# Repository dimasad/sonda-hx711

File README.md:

sonda-hx711
===========

Circuito para uma sonda aerodinâmica de 5 furos utilizando sensores de pressão
diferencial piezoresistivos e circuitos integrados HX711 para aquisição
de dados.

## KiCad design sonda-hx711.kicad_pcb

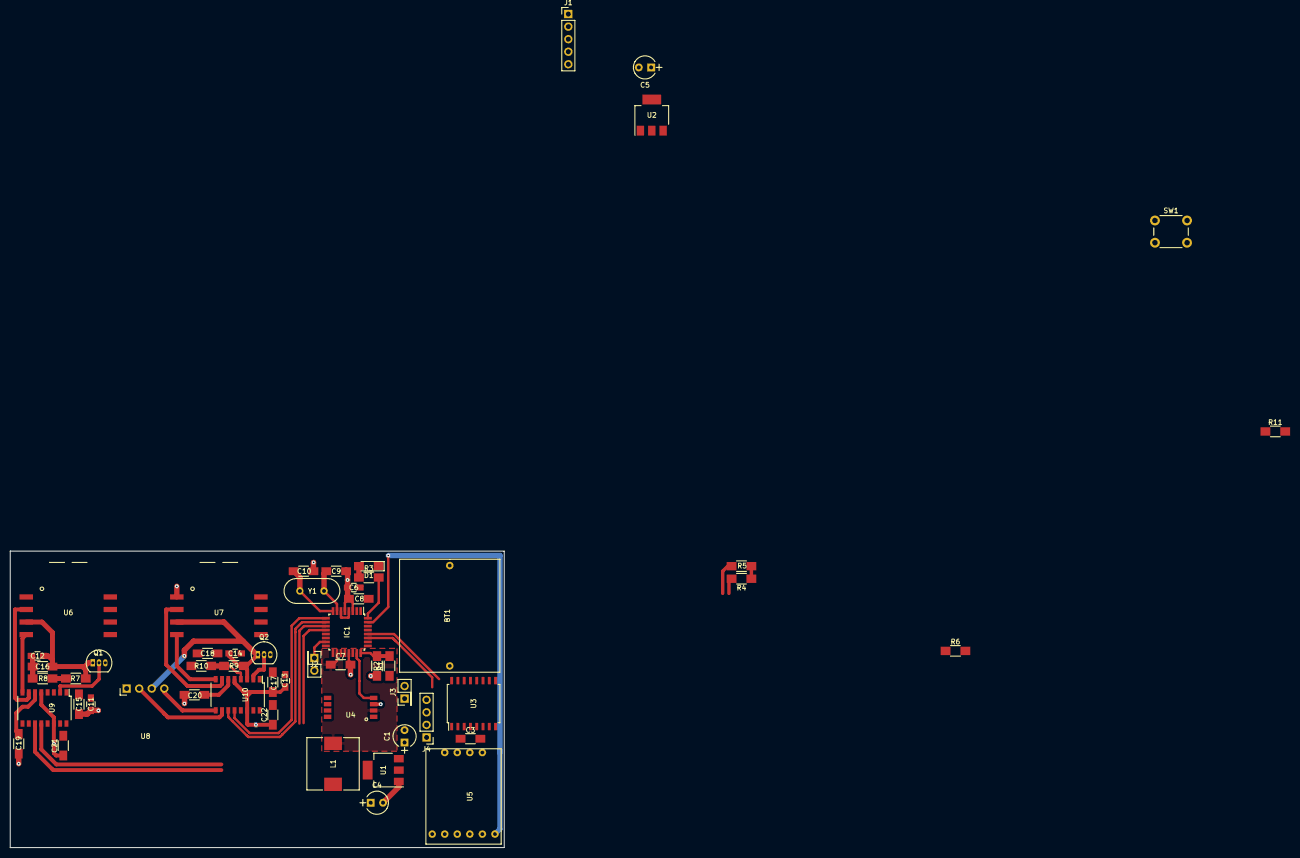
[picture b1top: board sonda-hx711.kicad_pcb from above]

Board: 2 copper layers, 100.0 x 60.0 mm, 54 parts (0 on the bottom side), 37 nets.

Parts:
BT1: 3V; SuporteBateria
C1, C4, C5: 22uF; CP_Radial_Tantal_D4.5mm_P2.50mm
C3, C7, C8, C15, C16, C17, C18, C19, C20, C21, C22: 100nF; C_1206_HandSoldering
C6, C11, C12, C13, C14: 10uF; C_0805_HandSoldering
C9, C10: 20pF; C_1206_HandSoldering
D1: status; LED_1206_HandSoldering
IC1: ATMEGA328P-A; TQFP-32_7x7mm_Pitch0.8mm
J1: CONN_01X05; Pin_Header_Straight_1x05_Pitch2.54mm
J2, J3: CONN_01X02; Pin_Header_Straight_2x01_Pitch2.54mm
J4: CONN_01X04; Pin_Header_Straight_1x04_Pitch2.54mm
L1: 10uH; L_10.4x10.4_H4.8
Q1, Q2: BC559; TO-92_Inline_Narrow_Oval
R1: 80k; R_1206_HandSoldering
R2: 50k; R_1206_HandSoldering
R3: 300R; R_1206_HandSoldering
R4, R5: R; R_1206_HandSoldering
R6, R7, R9: 10k; R_1206_HandSoldering
R8, R10: 2k2; R_1206_HandSoldering
R11: 4k7; R_1206_HandSoldering
SW1: Reset; SW_PUSH_6mm
U1: AP1117-50; SOT-223-3Lead_TabPin2
U2: AP1117-33; SOT-223-3Lead_TabPin2
U3: DS3231; SOIC-16W_7.5x10.3mm_Pitch1.27mm
U4: MPXA6115A; MPXH6115A
U5: DataLogger; OpenLog
U6, U7: MPXV2010; MPXV2010DP
U8: MPX10; Freescale_Case_344C-01-IssueB-Unibody
U9, U10: HX711; SOP-16_4.4x10.4mm_Pitch1.27mm
Y1: 16MHz; Crystal_HC49-U_Vertical

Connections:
+3V3: C5.1, J1.2, J4.1, R4.1, R5.1, U2.2
+5V: C3.1, C4.1, C6.1, C8.1, C11.2, C13.2, C15.2, C17.2, C21.2, C22.2, IC1.4, IC1.6, J1.1, L1.1, Q1.3, Q2.3, R6.1, R11.1, U1.2, U3.2, U5.3, U9.1, U9.15, U9.16, U10.1, U10.15, U10.16
+5VA: C7.1, IC1.18, L1.2, U4.2
+BATT: C1.1, J3.1, R1.1, U1.3, U2.3
/1WIRE: IC1.15, J2.1, R11.2
/BATT_MON: IC1.24, R1.2, R2.1
/PSTAT: IC1.23, U4.4
/RTC_INT: IC1.26, U3.3
/RX: IC1.30, J1.3
/SCL: IC1.28, J4.3, R5.2, U3.16
/SDA: IC1.27, J4.2, R4.2, U3.15
/TX: IC1.31, J1.4, U5.1
/alpha-Vout+: U7.2, U10.7
/alpha-Vout-: U7.4, U10.8
/alpha-beta-Vs: C14.2, C18.2, Q2.1, R9.1, U7.3, U8.3, U10.3
/angles_clk: IC1.10, U10.11
/angles_data: IC1.9, U10.12
/beta-Vout+: U8.2, U10.10
/beta-Vout-: U8.4, U10.9
/qbar_clk: IC1.12, U9.11
/qbar_data: IC1.11, U9.12
/status_LED: IC1.32, R3.2
GND: BT1.2, C1.2, C3.2, C4.2, C5.2, C6.2, C7.2, C8.2, C9.1, C10.1, C11.1, C12.1, C13.1, C14.1, C15.1, C16.1, C17.1, C18.1, C19.2, C20.2, C21.1, C22.1, D1.1, IC1.3, IC1.5, IC1.21, J1.5, J2.2, J3.2, J4.4, R2.2, R8.2, R10.2, SW1.2, U1.1, U2.1, U3.5, U3.6, U3.7, U3.8, U3.9, U3.10, U3.11, U3.12, U3.13, U4.3, U5.4, U6.1, U7.1, U8.1, U9.5, U9.14, U10.5, U10.14
unnamed: BT1.1, U3.14
unnamed: C9.2, IC1.7, Y1.2
unnamed: C10.2, IC1.8, Y1.1
unnamed: C12.2, C16.2, Q1.1, R7.1, U6.3, U9.3
unnamed: C19.1, U9.6
unnamed: C20.1, U10.6
unnamed: D1.2, R3.1
unnamed: IC1.29, R6.2, SW1.1
unnamed: Q1.2, U9.2
unnamed: Q2.2, U10.2
unnamed: R7.2, R8.1, U9.4
unnamed: R9.2, R10.1, U10.4
unnamed: U6.2, U9.7
unnamed: U6.4, U9.8

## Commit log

2017-10-10 Added schematic.
2017-10-12 Filling out the schematic.
2017-10-13 Finishing up the first revision of the schematic.
2017-10-15 Updated the schematic library pin types.
2017-10-15 Added onewire temperature sensor.
2017-10-16 Associating footprints.
2017-10-16 Started PCB layout.
2017-10-16 Adding custom footprints.
2017-10-16 Laying out board.
2017-10-17 Updated MPXV2010 footprint.
2017-10-18 Updated MPX10 footprint.
2017-10-19 Working on board layout.
